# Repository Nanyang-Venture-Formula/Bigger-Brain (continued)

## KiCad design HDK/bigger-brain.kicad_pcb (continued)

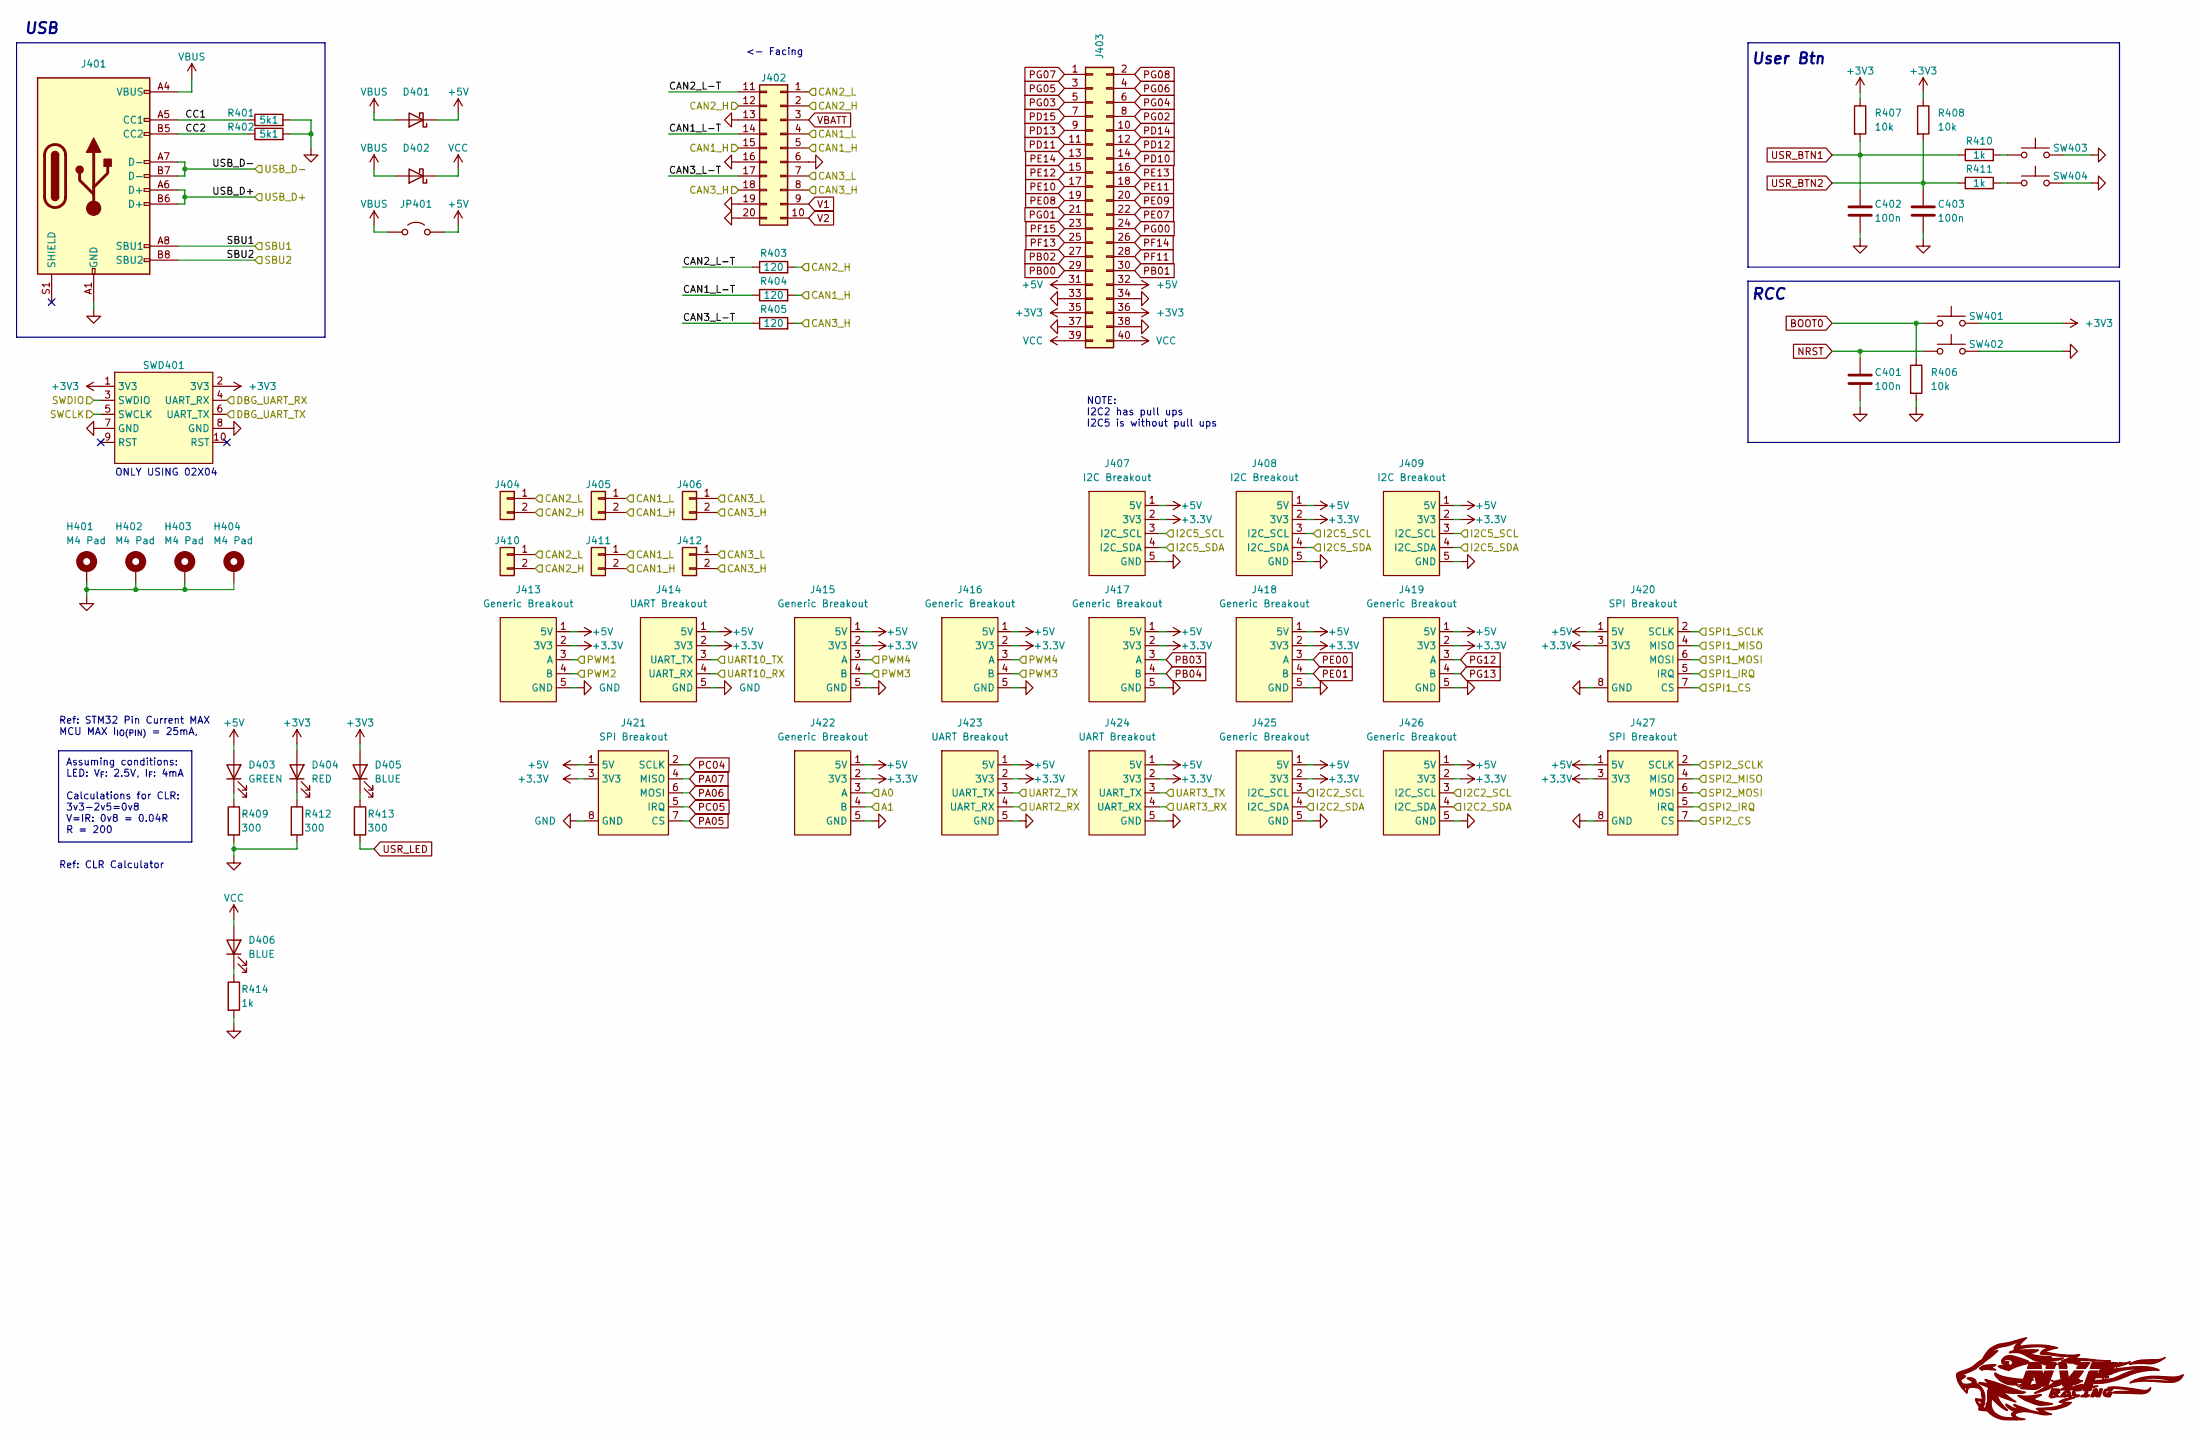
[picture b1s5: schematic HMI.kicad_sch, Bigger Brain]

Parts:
C401, C402, C403: 100n; C_0603_1608Metric; LCSC C14663
D401, D402: SS14; D_SMA; LCSC C2480
D403: GREEN; LED_0603_1608Metric; LCSC C434423
D404: RED; LED_0603_1608Metric; LCSC C2286
D405, D406: BLUE; LED_0603_1608Metric; LCSC C965807
H401, H402, H403, H404: M4 Pad; MountingHole_4.3mm_M4_DIN965_Pad_TopBottom
J401: USB_C; USBC_HRO_TYPE-C-31-M-12; LCSC C165948
J402: MicroFit_02x10V-H; LCSC C485575
J403: 2.54mm2x20V-H; LCSC C2894981
J404, J405, J406, J410, J411, J412: Conn_01x02; PH_01x02V-H; LCSC C2683610
J407, J408, J409: I2C Breakout; PH_01x05V-H; LCSC C157993
J413, J415, J416, J417, J418, J419, J422, J425, J426: Generic Breakout; PH_01x05V-H; LCSC C157993
J414, J423, J424: UART Breakout; PH_01x05V-H; LCSC C157993
J420, J421, J427: SPI Breakout; PHD_02x04V-H; LCSC C157975
JP401: Jumper_2_Open; PinHeader_1x02_P2.54mm_Vertical
R401, R402: 5k1; R_0603_1608Metric; LCSC C23186
R403, R404, R405: 120; R_1206_3216Metric; LCSC C17909
R406, R407, R408: 10k; R_0603_1608Metric; LCSC C25804
R409, R412, R413: 300; R_0603_1608Metric; LCSC C23025
R410, R411, R414: 1k; R_0603_1608Metric; LCSC C21190
SW401, SW402, SW403, SW404: SW_Push; PushBtn_TS-1187A-B-A-B; LCSC C318884
SWD401: PHD_02x04V-H; LCSC C157975

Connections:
/CanTrx1/CAN_H: J402.5, J402.15, J405.2, J411.2, R404.2; also elsewhere on the board
/CanTrx1/CAN_L: J402.4, J405.1, J411.1; also elsewhere on the board
/CanTrx2/CAN_H: J402.2, J402.12, J404.2, J410.2, R403.2; also elsewhere on the board
/CanTrx2/CAN_L: J402.1, J404.1, J410.1; also elsewhere on the board
/CanTrx3/CAN_H: J402.8, J402.18, J406.2, J412.2, R405.2; also elsewhere on the board
/CanTrx3/CAN_L: J402.7, J406.1, J412.1; also elsewhere on the board
/HMI/CAN1_L-T: J402.14, R404.1
/HMI/CAN2_L-T: J402.11, R403.1
/HMI/CAN3_L-T: J402.17, R405.1
/HMI/CC1: J401.A5 (CC1), R401.1
/HMI/CC2: J401.B5 (CC2), R402.1
/I2C2_SCL: J425.4 (I2C_SDA), J426.4 (I2C_SDA); also elsewhere on the board
/I2C2_SDA: J425.3 (I2C_SCL), J426.3 (I2C_SCL); also elsewhere on the board
/I2C5_SCL: J407.4 (I2C_SDA), J408.4 (I2C_SDA), J409.4 (I2C_SDA); also elsewhere on the board
/I2C5_SDA: J407.3 (I2C_SCL), J408.3 (I2C_SCL), J409.3 (I2C_SCL); also elsewhere on the board
/SPI1_CS: J420.7 (CS); also elsewhere on the board
/SPI1_IRQ: J420.5 (IRQ); also elsewhere on the board
/SPI1_MISO: J420.4 (MISO); also elsewhere on the board
/SPI1_MOSI: J420.6 (MOSI); also elsewhere on the board
/SPI1_SCLK: J420.2 (SCLK); also elsewhere on the board
/SPI2_CS: J427.7 (CS); also elsewhere on the board
/SPI2_IRQ: J427.5 (IRQ); also elsewhere on the board
/SPI2_MISO: J427.4 (MISO); also elsewhere on the board
/SPI2_MOSI: J427.6 (MOSI); also elsewhere on the board
/SPI2_SCLK: J427.2 (SCLK); also elsewhere on the board
/SWCLK: J401.B8 (SBU2), SWD401.5 (SWCLK); also elsewhere on the board
/SWDIO: J401.A8 (SBU1), SWD401.3 (SWDIO); also elsewhere on the board
/UART1_RX: SWD401.4 (UART_RX); also elsewhere on the board
/UART1_TX: SWD401.6 (UART_TX); also elsewhere on the board
/UART2_RX: J423.4 (UART_RX); also elsewhere on the board
/UART2_TX: J423.3 (UART_TX); also elsewhere on the board
/UART3_RX: J424.4 (UART_RX); also elsewhere on the board
/UART3_TX: J424.3 (UART_TX); also elsewhere on the board
/UART10_RX: J414.4 (UART_RX); also elsewhere on the board
/UART10_TX: J414.3 (UART_TX); also elsewhere on the board
BOOT0: R406.1, SW401.1; also elsewhere on the board
GND: C401.2, C402.2, C403.2, H401.1, H402.1, H403.1, H404.1, J401.A1 (GND), J401.A12 (GND), J401.B1 (GND), J401.B12 (GND), J402.6, J402.13, J402.16, J402.19, J402.20, J403.33, J403.34, J403.37, J403.38, J407.5 (GND), J408.5 (GND), J409.5 (GND), J413.5 (GND), J414.5 (GND), J415.5 (GND), J416.5 (GND), J417.5 (GND), J418.5 (GND), J419.5 (GND), J420.8 (GND), J421.8 (GND), J422.5 (GND), J423.5 (GND), J424.5 (GND), J425.5 (GND), J426.5 (GND), J427.8 (GND), R401.2, R402.2, R406.2, R409.2, R412.2, R414.2, SW402.2, SW403.2, SW404.2, SWD401.7 (GND), SWD401.8 (GND); also elsewhere on the board
MCU-3.3V: D404.2 (A), D405.2 (A), J403.35, J403.36, J407.2 (3V3), J408.2 (3V3), J409.2 (3V3), J413.2 (3V3), J414.2 (3V3), J415.2 (3V3), J416.2 (3V3), J417.2 (3V3), J418.2 (3V3), J419.2 (3V3), J420.3 (3V3), J421.3 (3V3), J422.2 (3V3), J423.2 (3V3), J424.2 (3V3), J425.2 (3V3), J426.2 (3V3), J427.3 (3V3), R407.1, R408.1, SW401.2, SWD401.1 (3V3), SWD401.2 (3V3); also elsewhere on the board
NRST: C401.1, SW402.1; also elsewhere on the board
unnamed: D403.1 (K), R409.1
unnamed: D404.1 (K), R412.1
unnamed: D405.1 (K), R413.1
unnamed: D406.1 (K), R414.1
unnamed: R410.2, SW403.1
unnamed: R411.2, SW404.1
PA05: J421.7 (CS); also elsewhere on the board
PA06: J421.6 (MOSI); also elsewhere on the board
PA07: J421.4 (MISO); also elsewhere on the board
PB00: J403.29; also elsewhere on the board
PB01: J403.30; also elsewhere on the board
PB02: J403.27; also elsewhere on the board
PB03: J417.3 (A); also elsewhere on the board
PB04: J417.4 (B); also elsewhere on the board
PC04: J421.2 (SCLK); also elsewhere on the board
PC05: J421.5 (IRQ); also elsewhere on the board
PD10: J403.14; also elsewhere on the board
PD11: J403.11; also elsewhere on the board
PD12: J403.12; also elsewhere on the board
PD13: J403.9; also elsewhere on the board
PD14: J403.10; also elsewhere on the board
PD15: J403.7; also elsewhere on the board
PE00: J418.3 (A); also elsewhere on the board
PE01: J418.4 (B); also elsewhere on the board
PE05: J413.4 (B); also elsewhere on the board
PE06: J413.3 (A); also elsewhere on the board
PE07: J403.22; also elsewhere on the board
PE08: J403.19; also elsewhere on the board
PE09: J403.20; also elsewhere on the board
PE10: J403.17; also elsewhere on the board
PE11: J403.18; also elsewhere on the board
PE12: J403.15; also elsewhere on the board
PE13: J403.16; also elsewhere on the board
PE14: J403.13; also elsewhere on the board
PF02: J415.3 (A), J416.3 (A); also elsewhere on the board
PF03: J415.4 (B), J416.4 (B); also elsewhere on the board
PF04: J422.3 (A); also elsewhere on the board
PF05: J422.4 (B); also elsewhere on the board
PF11: J403.28; also elsewhere on the board
PF13: J403.25; also elsewhere on the board
PF14: J403.26; also elsewhere on the board
PF15: J403.23; also elsewhere on the board
PG00: J403.24; also elsewhere on the board
PG01: J403.21; also elsewhere on the board
PG02: J403.8; also elsewhere on the board
PG03: J403.5; also elsewhere on the board
PG04: J403.6; also elsewhere on the board
PG05: J403.3; also elsewhere on the board
PG06: J403.4; also elsewhere on the board
PG07: J403.1; also elsewhere on the board
PG08: J403.2; also elsewhere on the board
PG12: J419.3 (A); also elsewhere on the board
PG13: J419.4 (B); also elsewhere on the board
PP-5.0V: D401.1 (K), D403.2 (A), J403.31, J403.32, J407.1 (5V), J408.1 (5V), J409.1 (5V), J413.1 (5V), J414.1 (5V), J415.1 (5V), J416.1 (5V), J417.1 (5V), J418.1 (5V), J419.1 (5V), J420.1 (5V), J421.1 (5V), J422.1 (5V), J423.1 (5V), J424.1 (5V), J425.1 (5V), J426.1 (5V), J427.1 (5V), JP401.2 (B); also elsewhere on the board
USB_D+: J401.A6 (D+), J401.B6 (D+); also elsewhere on the board
USB_D-: J401.A7 (D-), J401.B7 (D-); also elsewhere on the board
USR_BTN1: C402.1, R407.2, R410.1; also elsewhere on the board
USR_BTN2: C403.1, R408.2, R411.1; also elsewhere on the board
USR_LED: R413.2; also elsewhere on the board
V1: J402.9; also elsewhere on the board
V2: J402.10; also elsewhere on the board
VBATT: J402.3; also elsewhere on the board
VBUS: D401.2 (A), D402.2 (A), J401.A4 (VBUS), J401.A9 (VBUS), J401.B4 (VBUS), J401.B9 (VBUS), JP401.1 (A)
VCC: D402.1 (K), D406.2 (A), J403.39, J403.40; also elsewhere on the board

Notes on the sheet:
NOTE: I2C2 has pull ups I2C5 is without pull ups
USB
<- Facing
Ref: STM32 Pin Current MAX MCU MAX I_{IO(PIN)} = 25mA,
Ref: CLR Calculator
Assuming conditions: LED: V_{F}: 2.5V, I_{F}: 4mA Calculations for CLR: 3v3-2v5=0v8 V=IR: 0v8 = 0.04R R = 200
ONLY USING 02X04
RCC
User Btn

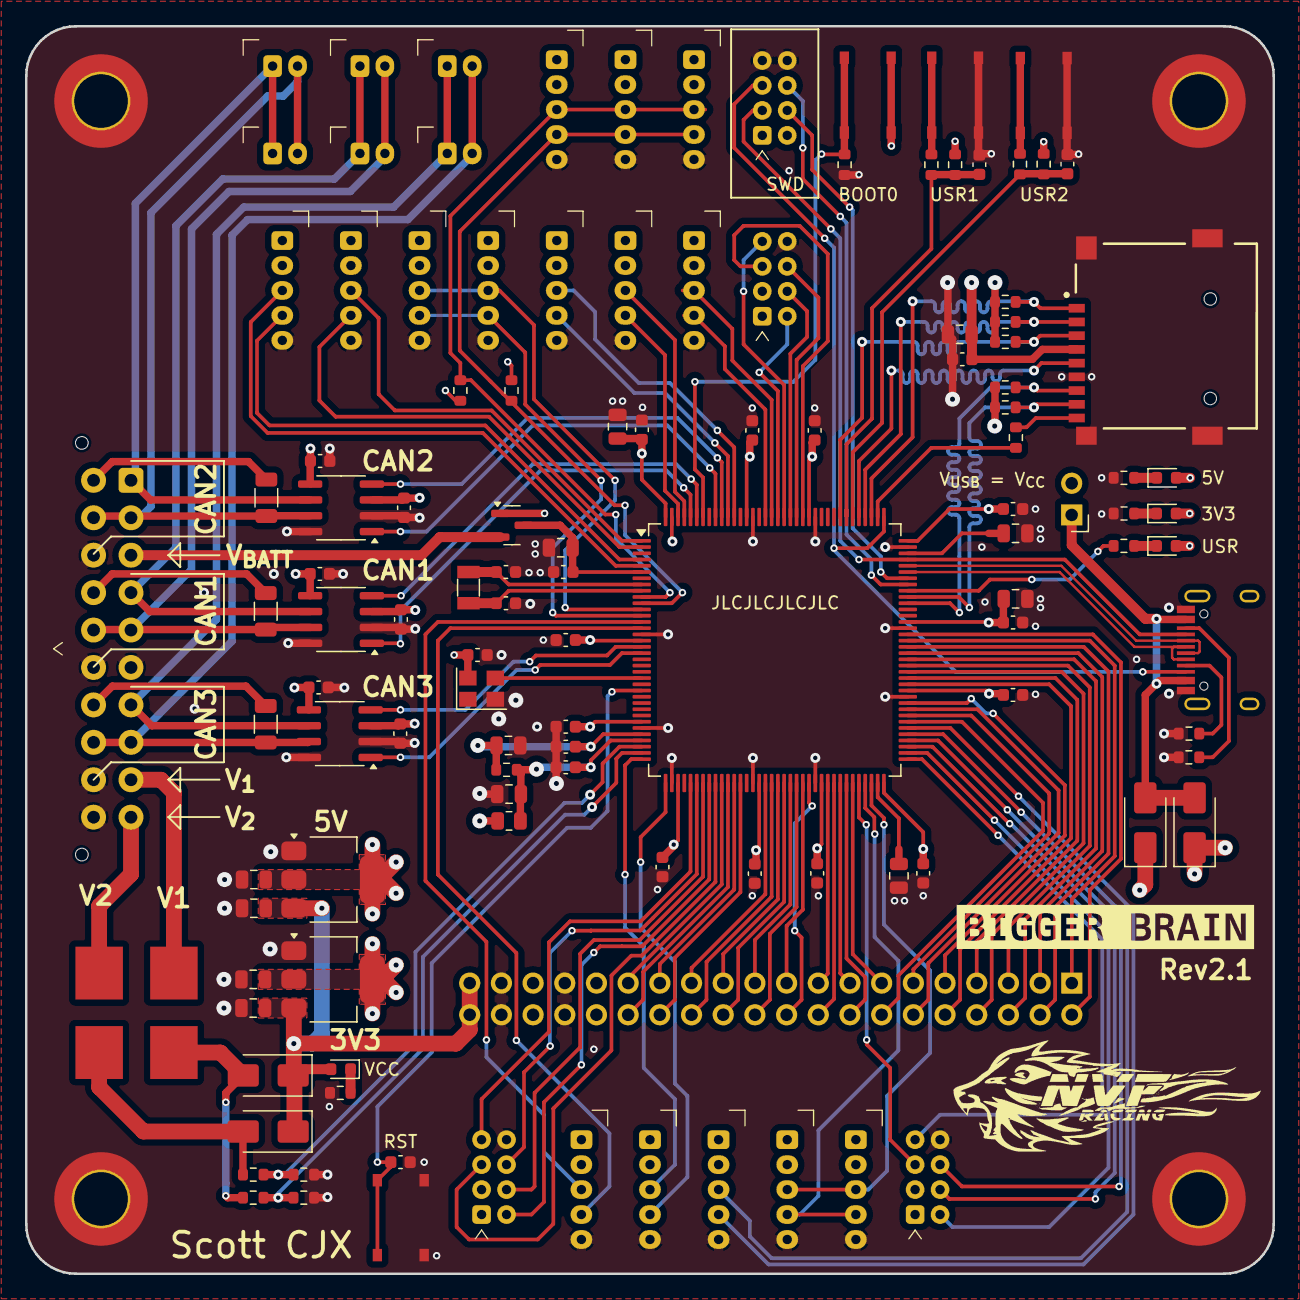
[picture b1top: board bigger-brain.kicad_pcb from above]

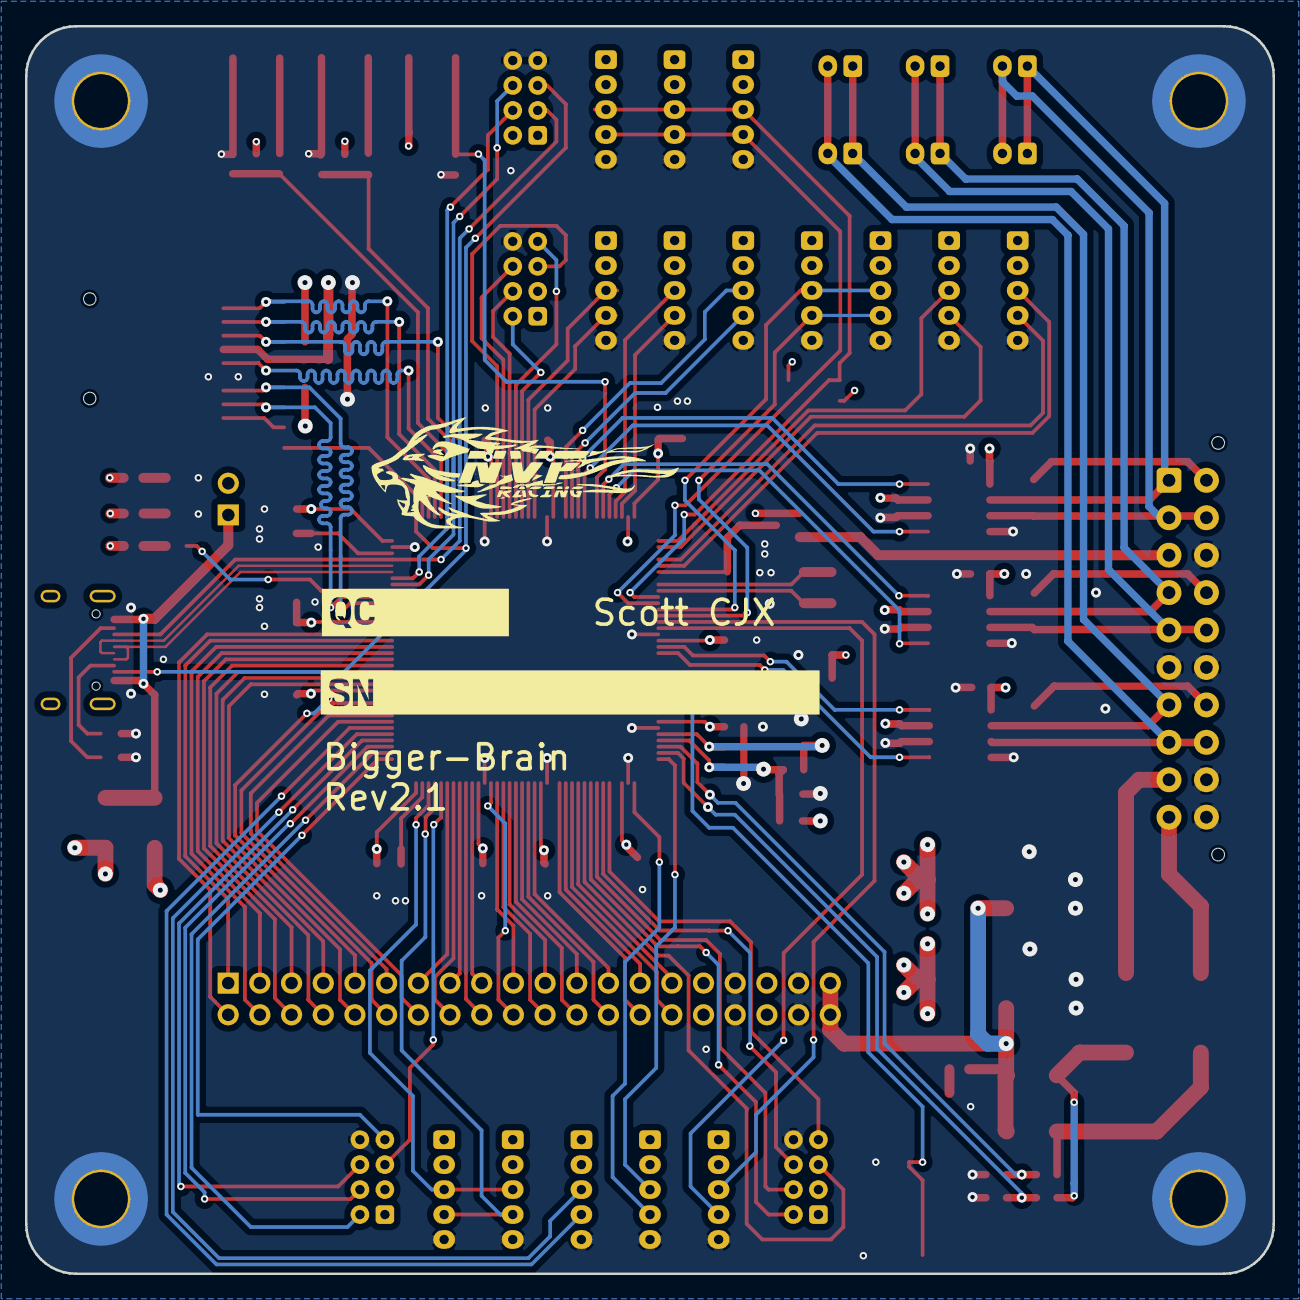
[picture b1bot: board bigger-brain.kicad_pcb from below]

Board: 4 copper layers, 100.0 x 100.0 mm, 128 parts (2 on the bottom side), 129 nets.

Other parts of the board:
kibuzzard-65AE28D0: G***; kibuzzard-65AE28D0
kibuzzard-65BA50A4: G***; kibuzzard-65BA50A4
kibuzzard-65BA50D8: G***; kibuzzard-65BA50D8

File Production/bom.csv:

Designator,Footprint,Quantity,Value,LCSC Part #
"C101, C201, C202, C203, C204, C205, C206, C207, C208, C209, C210, C211, C213, C215, C217, C221, C301, C401, C402, C403, C501, C502, C601, C602, C701, C702",0603,26,100n,C14663
"C103, C104",0603,2,15p,C1644
C212,0805,1,4u7,C1779
"C214, C216, C218, C222, C302",0805,5,1u,C28323
"C219, C220, C223, C224, C227, C228",0805,6,2u2,C377773
D201,SOT-23,1,BAV70,C68978
"D202, D203, D401, D402",D_SMA,4,SS14,C2480
D403,0603,1,GREEN,C434423
D404,0603,1,RED,C2286
"D405, D406",0603,2,BLUE,C965807
"F201, F202",FUSE-Littelfuse_Nano2_154x,2,1A,C206910
"H401, H402, H403, H404",MountingHole_4.3mm_M4_DIN965_Pad_TopBottom,4,M4 Pad,-
J301,TFCard_TF-01A,1,TF-01A,C91145
J401,USBC_HRO_TYPE-C-31-M-12,1,USB_C,C165948
J402,MicroFit_02x10V-H,1,Molex_Micro-Fit_3.0_43045-2012_2x10_P3.00mm_Vertical,C485575
J403,2.54mm2x20V-H,1,2x20V-H,C2894981
"J404, J405, J406, J410, J411, J412",PH_01x02V-H,6,Conn_01x02,C2683610
"J407, J408, J409",PH_01x05V-H,3,I2C Breakout,C157993
"J413, J415, J416, J417, J418, J419, J422, J425, J426",PH_01x05V-H,9,Generic Breakout,C157993
"J414, J423, J424",PH_01x05V-H,3,UART Breakout,C157993
"J420, J421, J427",PHD_02x04V-H,3,SPI Breakout,C157975
JP401,PinHeader_1x02_P2.54mm_Vertical,1,Jumper_2_Open,-
L201,0805,1,100MHz,C1015
"R101, R102, R202, R204, R401, R402",0603,6,5k1,C23186
R201,0603,1,47,C23182
"R203, R205, R410, R411, R414",0603,5,1k,C21190
"R301, R302, R303, R304, R305",0603,5,47k,C25819
"R306, R406, R407, R408",0603,4,10k,C25804
"R403, R404, R405",1206,3,120,C17909
"R409, R412, R413",0603,3,300,C23025
"SW401, SW402, SW403, SW404",PushBtn_TS-1187A-B-A-B,4,SW_Push,C318884
SWD401,PHD_02x04V-H,1,~,C157975
U101,LQFP-144_20x20mm_P0.5mm,1,STM32H723ZGTx,C730146
U201,SOT-223-3_TabPin2,1,AMS1117-3.3,C6186
U203,SOT-223-3_TabPin2,1,AMS1117-5.0,C6187
"U501, U601, U701",SOIC-8_3.9x4.9mm_P1.27mm,3,TJA1042T-3,C132227
X101,Crystal_SMD_3225-4Pin_3.2x2.5mm,1,25MHz ±10ppm,C669088
Y101,Crystal_SMD_3215-2Pin_3.2x1.5mm,1,32.768kHz 12.5pF ±20ppm,C32346

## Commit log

2024-01-23 Initialize gh-pages
2024-01-23 Moving files docs/* LICENSE using main
2024-01-23 Deploying to gh-pages from @ Nanyang-Venture-Formula/Bigger-Brain@bf46e201431f0832cedabf7d1930b928110b4986 🚀
2024-01-23 Deploying to gh-pages from @ Nanyang-Venture-Formula/Bigger-Brain@9bb961c5cf9fe9f651ec44afec5c6be612246c10 🚀
2024-01-23 refactored
2024-01-23 Deploying to gh-pages from @ Nanyang-Venture-Formula/Bigger-Brain@b05194056bf7e9350b8a63c62a51a15df93f3bbd 🚀
2024-01-24 updated WIP
2024-01-24 updated ignore
2024-01-24 Deploying to gh-pages from @ Nanyang-Venture-Formula/Bigger-Brain@ddce3e3baf84d1258ea70a7d695fc1a9ec02dae2 🚀
2024-01-24 rm files
2024-01-24 Deploying to gh-pages from @ Nanyang-Venture-Formula/Bigger-Brain@1e1c5b7f0298c231acf4b362ead1f9a99ee8fe3f 🚀
2024-01-24 Deploying to gh-pages from @ Nanyang-Venture-Formula/Bigger-Brain@f346a9555b9a3091549b642cdf5a10063fae5813 🚀
2024-01-24 updated gitignore
2024-01-24 Deploying to gh-pages from @ Nanyang-Venture-Formula/Bigger-Brain@42099d0ca761c9f7f09c89295aeb18c67a49205e 🚀
2024-01-31 added rev1-final
2024-01-31 Deploying to gh-pages from @ Nanyang-Venture-Formula/Bigger-Brain@9f00a1a5bacef60cb4c49446823402ba3fb37510 🚀
2024-01-31 fixed bom
2024-02-02 freeze rev1
2024-02-09 rm lck
2024-03-01 freeze rev1.1
2024-03-05 updated rev2
2024-03-17 freeze rev2
2024-03-18 updated docs
2024-04-08 Deploying to gh-pages from @ Nanyang-Venture-Formula/Bigger-Brain@e4f2628f5049cec85f73851d7b85ae3f4333c5d2 🚀
2024-04-08 updated rev2.1
2024-04-08 removed sym-lib-table
2024-04-08 added fab and ibom
2024-04-08 fixed readme
2024-04-08 fixed ibom
2025-03-22 Deploying to gh-pages from @ Nanyang-Venture-Formula/Bigger-Brain@63b77f029214ad98e86b0b2e59daf12e33ce8c80 🚀
